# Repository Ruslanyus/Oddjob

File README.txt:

Oddjob project is based on the Photoduino project.
My main objective is to add a new interface to this project, I have added a touch screen with several updated.

Logos are stored on the SD card, UTFT library and tools are used to generate logo.

You have to copy logos on RAW format into the root of your SD card.

To do list:
-unbug the display: some case the text is too long and wrote out of display memory, I have to fix this issue

-The date and time module is not coded to log all information with date and time
-luxmeter display information but information is display without presentation.

I publish more information on the www.godreau.fr website with photos.

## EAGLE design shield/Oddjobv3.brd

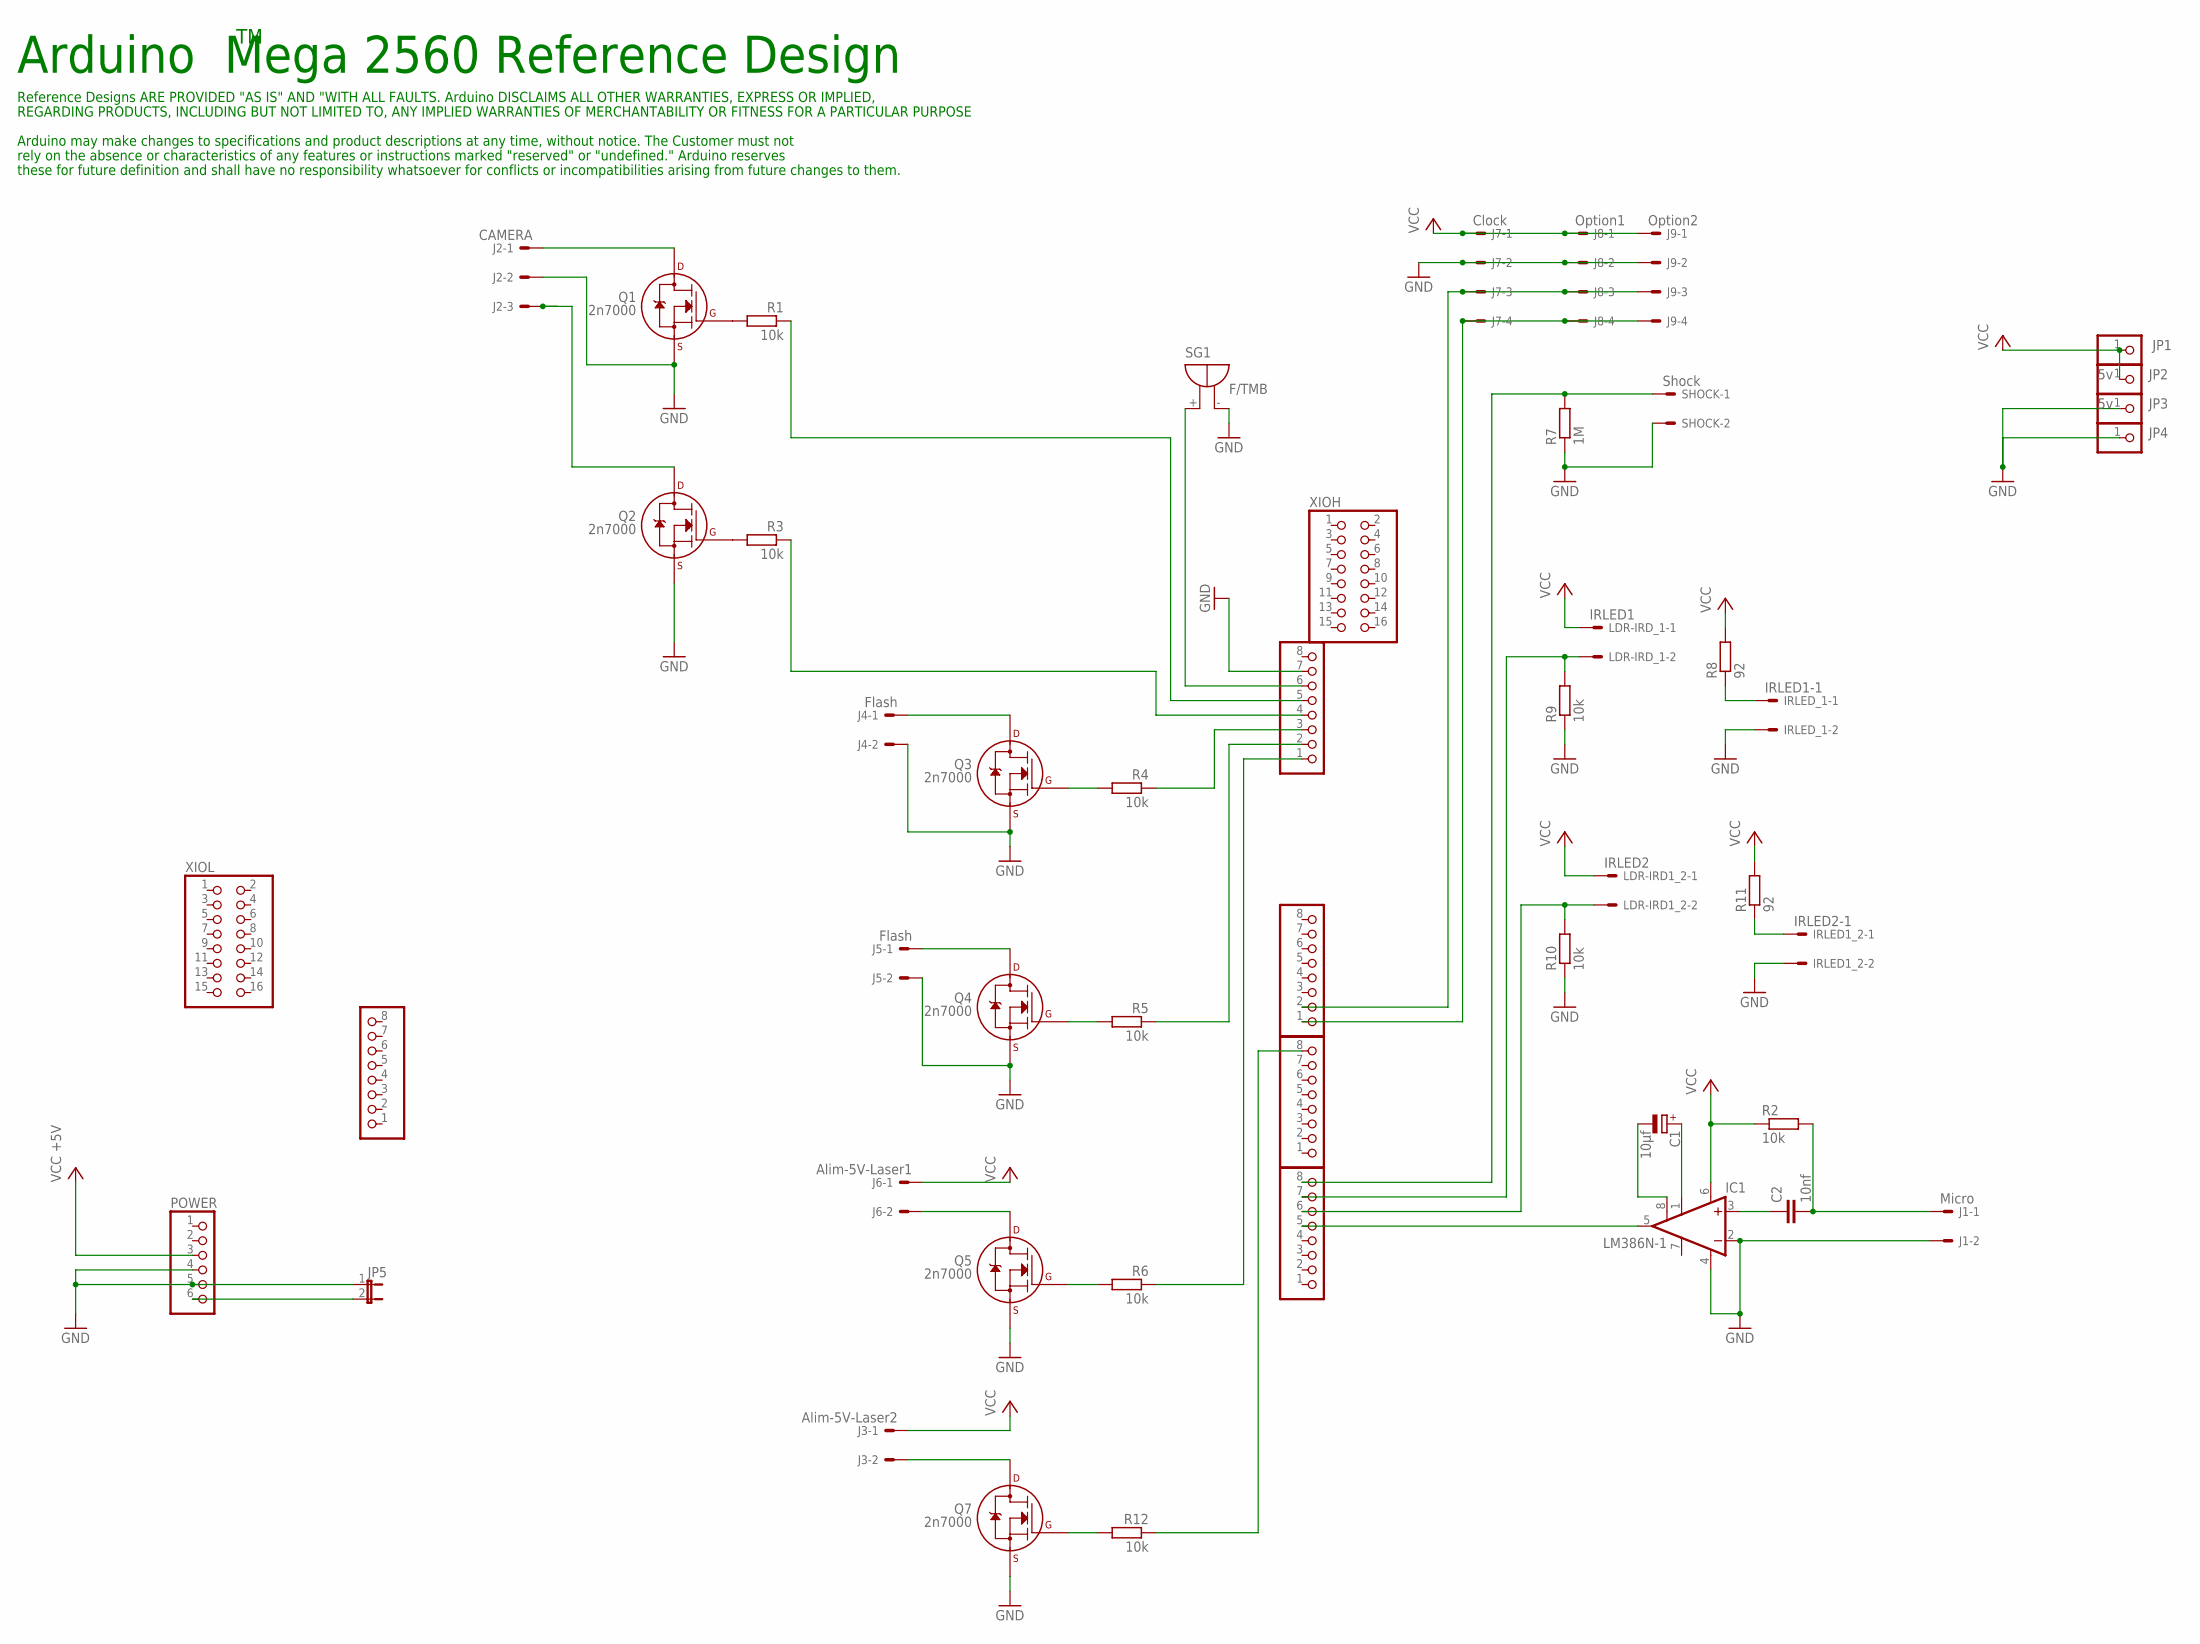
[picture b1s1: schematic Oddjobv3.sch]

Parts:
ADCH: PINHD-1X8; 1X08
ADCL: PINHD-1X8; 1X08
C1: 10µf; E2,5-6
C2: 10nf; C050-025X075
COMMUNICATION: PINHD-1X8; 1X08
IC1: LM386N-1; DIL08
IRLED1_2: IRLED2-1; 6410-02
IRLED_1: IRLED1-1; 6410-02
J1: Micro; 6410-02
J2: CAMERA; 6410-03
J3: Alim-5V-Laser2; 6410-02
J4, J5: Flash; 6410-02
J6: Alim-5V-Laser1; 6410-02
J7: Clock; 6410-04
J8: Option1; 6410-04
J9: Option2; 6410-04
JP1, JP2: 5v; 1X01
JP3, JP4: PINHD-1X1; 1X01
JP5: JP1E; JP1
LDR-IRD1_2: IRLED2; 6410-02
LDR-IRD_1: IRLED1; 6410-02
POWER: PINHD-1X6; 1X06
PWMH-NUMERIC: PINHD-1X8; 1X08
PWML: PINHD-1X8; 1X08
Q1, Q2, Q3, Q4, Q5, Q7: 2n7000; TO-92
R1, R2, R3, R4, R5, R6, R9, R10, R12: 10k; 0207/7
R7: 1M; 0207/7
R8, R11: 92; 0207/7
SG1: F/TMB
SHOCK: Shock; 6410-02
XIOH: PINHD-2X8; 2X08
XIOL: PINHD-2X8; 2X08

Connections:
GND: IC1.2 (-IN), IC1.4 (GND), IRLED1_2.2, IRLED_1.2, J1.2, J2.2, J4.2, J5.2, J7.2, J8.2, J9.2, JP3.1, JP4.1, JP5.1, POWER.4, POWER.5, PWMH-NUMERIC.7, Q1.1 (S), Q2.1 (S), Q3.1 (S), Q4.1 (S), Q5.1 (S), Q7.1 (S), R7.1, R9.1, R10.1, SG1.-, SHOCK.2
unnamed: Q1.2 (G), R1.2
unnamed: J2.1, Q1.3 (D)
unnamed: C1.+, IC1.1 (GAIN)
unnamed: C1.-, IC1.8 (GAIN)
unnamed: C2.1, IC1.3 (+IN)
unnamed: C2.2, J1.1, R2.2
unnamed: Q2.2 (G), R3.2
unnamed: J2.3, Q2.3 (D)
unnamed: PWMH-NUMERIC.6, SG1.+
unnamed: Q3.2 (G), R4.2
unnamed: J4.1, Q3.3 (D)
unnamed: J6.2, Q5.3 (D)
unnamed: Q4.2 (G), R5.2
unnamed: J5.1, Q4.3 (D)
unnamed: Q5.2 (G), R6.2
unnamed: IRLED_1.1, R8.1
unnamed: ADCL.7, LDR-IRD_1.2, R9.2
unnamed: ADCL.6, LDR-IRD1_2.2, R10.2
unnamed: IRLED1_2.1, R11.1
unnamed: PWMH-NUMERIC.1, R6.1
unnamed: PWMH-NUMERIC.5, R1.1
unnamed: PWMH-NUMERIC.2, R5.1
unnamed: PWMH-NUMERIC.4, R3.1
unnamed: PWMH-NUMERIC.3, R4.1
unnamed: ADCL.5, IC1.5 (OUT)
unnamed: Q7.2 (G), R12.2
unnamed: J3.2, Q7.3 (D)
unnamed: ADCL.8, R7.2, SHOCK.1
unnamed: COMMUNICATION.1, J7.4, J8.4, J9.4
unnamed: PWML.8, R12.1
unnamed: COMMUNICATION.2, J7.3, J8.3, J9.3
unnamed: JP5.2, POWER.6
VCC: IC1.6 (VS), J3.1, J6.1, J7.1, J8.1, J9.1, JP1.1, JP2.1, LDR-IRD1_2.1, LDR-IRD_1.1, POWER.3, R2.1, R8.2, R11.2

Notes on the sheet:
Arduino Mega 2560 Reference Design
Reference Designs ARE PROVIDED "AS IS" AND "WITH ALL FAULTS. Arduino DISCLAIMS ALL OTHER WARRANTIES, EXPRESS OR IMPLIED,
Arduino may make changes to specifications and product descriptions at any time, without notice. The Customer must not
REGARDING PRODUCTS, INCLUDING BUT NOT LIMITED TO, ANY IMPLIED WARRANTIES OF MERCHANTABILITY OR FITNESS FOR A PARTICULAR PURPOSE
rely on the absence or characteristics of any features or instructions marked "reserved" or "undefined." Arduino reserves
these for future definition and shall have no responsibility whatsoever for conflicts or incompatibilities arising from future changes to them.

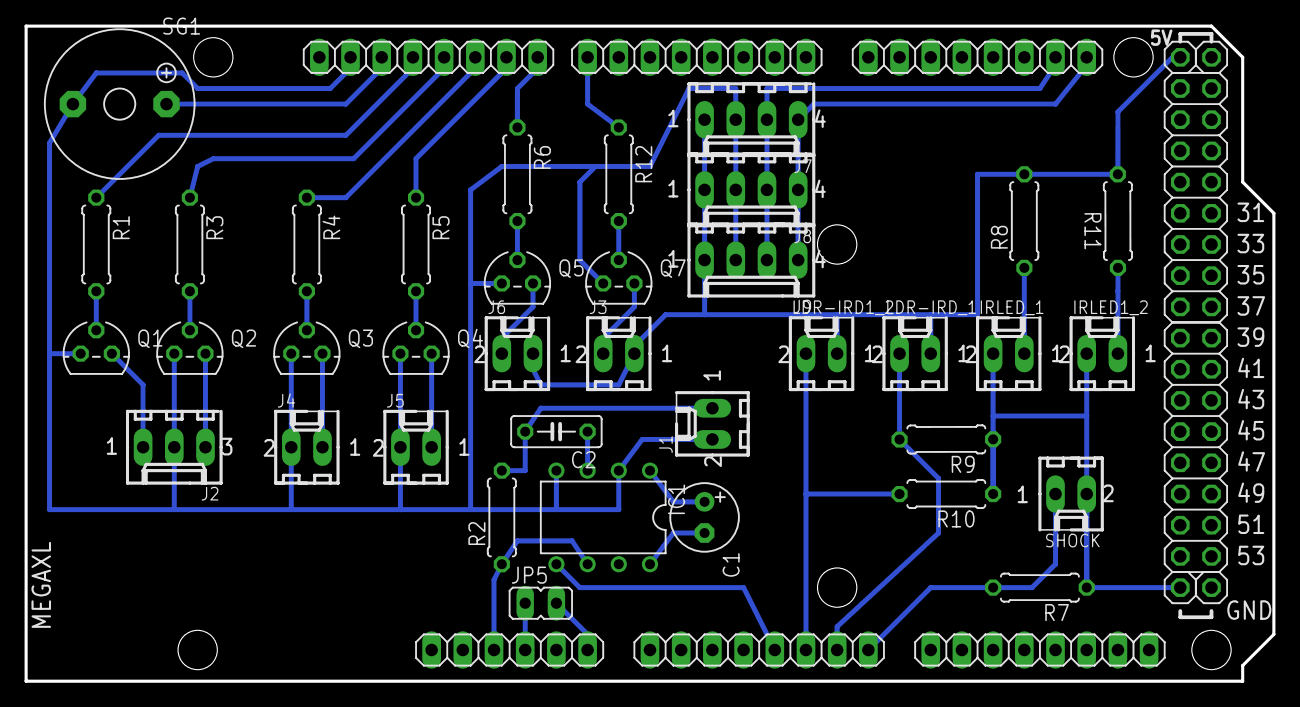
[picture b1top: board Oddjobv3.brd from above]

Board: 1 copper layer, 101.6 x 53.3 mm, 49 parts (0 on the bottom side), 34 nets.

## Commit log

2013-05-23 Beta version
    Beta version: running but bugs could be present and few functionalities
    are not finish or validated
2013-05-23 first update
    add to do and more informations
2013-05-25 add photo
2013-05-31 Add clean mode for solenoid
    Add clean mode for solenoid and Lux meter mode
2013-05-31 Release 1.3
    Bug fix and source cleanup
